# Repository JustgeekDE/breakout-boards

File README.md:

# breakout-boards
A variety of breakoutboards for various packages and modules

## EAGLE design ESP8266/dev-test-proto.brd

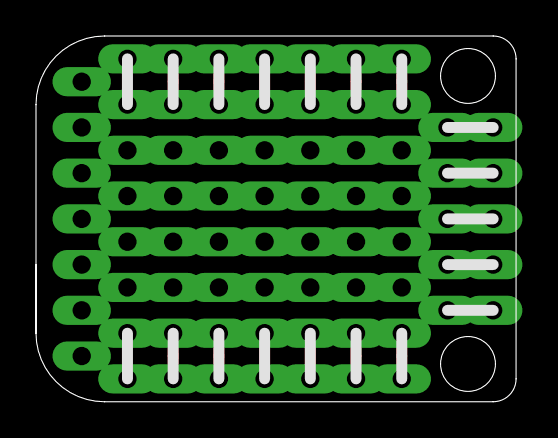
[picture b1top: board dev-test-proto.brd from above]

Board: 2 copper layers, 26.7 x 20.3 mm, 20 parts (0 on the bottom side), 19 nets.

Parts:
CON1, CON4, CON5, CON6, CON7, CON8, CON9, CON14, CON15, CON16, CON17, CON18, CON19, CON21, CON22: PINHEADER-100MIL-1X4-NOSILK
E$1, E$2, E$3: PINHEADER-100MIL-1X3-NOSILK
E$4, E$5: PINHEADER-100MIL-1X2-NOSILK

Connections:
+3V3: CON6.1, CON6.2
+5V: CON4.3, CON4.4
GND: CON21.3, CON21.4
GPIO0: CON22.1, CON22.2
GPIO2: CON15.1, CON15.2
GPIO12: CON14.1, CON14.2
GPIO13: CON7.1, CON7.2
GPIO14: CON1.1, CON1.2
GPIO15: CON18.1, CON18.2
GPIO16: CON8.3, CON8.4
RESET: CON9.3, CON9.4
RX: CON17.3, CON17.4
S$1: CON5.3, CON5.4
S$2: E$2.3, E$3.3
S$3: E$2.2, E$3.2
S$4: E$2.1, E$3.1
S$5: E$4.2, E$5.2
S$6: E$4.1, E$5.1
TX: CON16.3, CON16.4

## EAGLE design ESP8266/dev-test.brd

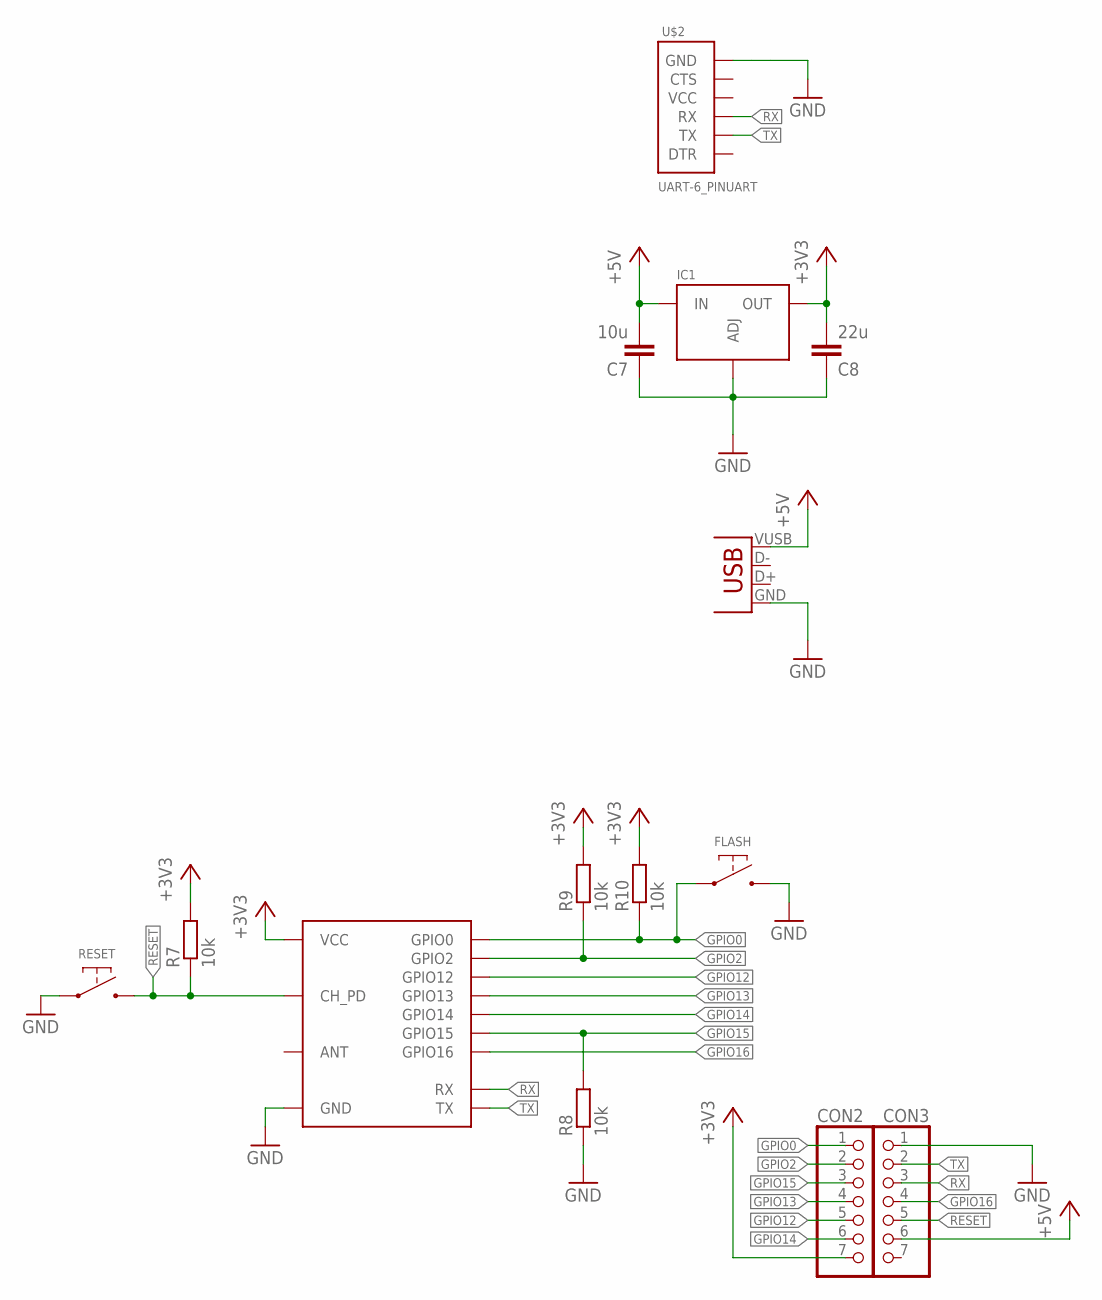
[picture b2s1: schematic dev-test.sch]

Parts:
C7: 10u; C0805
C8: 22u; C0805
CON1: USBMICRO-NO_CENTER; USB-MICRO-SMD-NO_CENTER
CON2, CON3: GENERIC-1X7THT; PINHEADER-100MIL-1X7
FLASH: SWITCH-DEFAULT_OFF-SMD-2_PIN; SWITCH-SMD-2_PIN-DX
IC1: REGULATOR-LM317-SOT223; SOT223
R7, R8, R9, R10: 10k; R0603
RESET: SWITCH-DEFAULT_OFF-SMD-2_PIN; SWITCH-SMD-2_PIN-DX
U$1: ESP8266-03; ESP8266-ESP-03
U$2: UART-6_PINUART; ANGLE-1X6

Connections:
+3V3: C8.2, CON2.7, IC1.2 (OUT), IC1.4 (OUT), R7.2, R9.2, R10.2, U$1.P$8 (VCC)
+5V: C7.2, CON1.VUSB (VBUS), CON3.6, IC1.3 (IN)
GND: C7.1, C8.1, CON1.GND, CON3.1, FLASH.P$2, IC1.1 (ADJ), R8.1, RESET.P$1, U$1.P$1 (GND), U$2.1 (GND)
GPIO0: CON2.1, FLASH.P$1, R10.1, U$1.P$14 (GPIO0)
GPIO2: CON2.2, R9.1, U$1.P$13 (GPIO2)
GPIO12: CON2.5, U$1.P$10 (GPIO12)
GPIO13: CON2.4, U$1.P$11 (GPIO13)
GPIO14: CON2.6, U$1.P$9 (GPIO14)
GPIO15: CON2.3, R8.2, U$1.P$12 (GPIO15)
GPIO16: CON3.4, U$1.P$5 (GPIO16)
RESET: CON3.5, R7.1, RESET.P$2, U$1.P$6 (CH_PD)
RX: CON3.3, U$1.P$4 (RX), U$2.4 (RX)
TX: CON3.2, U$1.P$3 (TX), U$2.5 (TX)

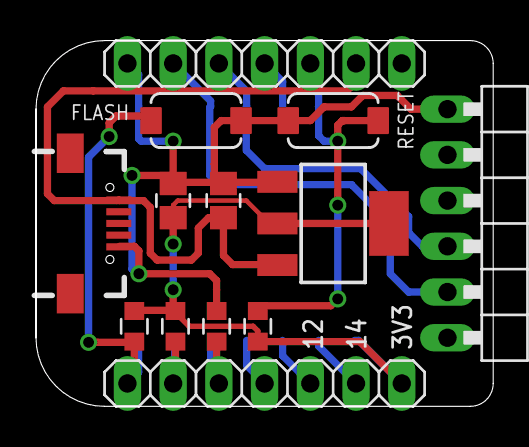
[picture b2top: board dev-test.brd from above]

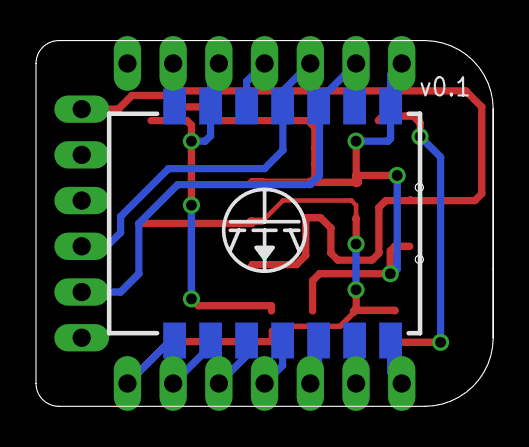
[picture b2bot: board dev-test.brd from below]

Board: 2 copper layers, 25.4 x 20.3 mm, 15 parts (2 on the bottom side), 13 nets.

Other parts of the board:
U$3: LOGO-JUSTGEEK-XS

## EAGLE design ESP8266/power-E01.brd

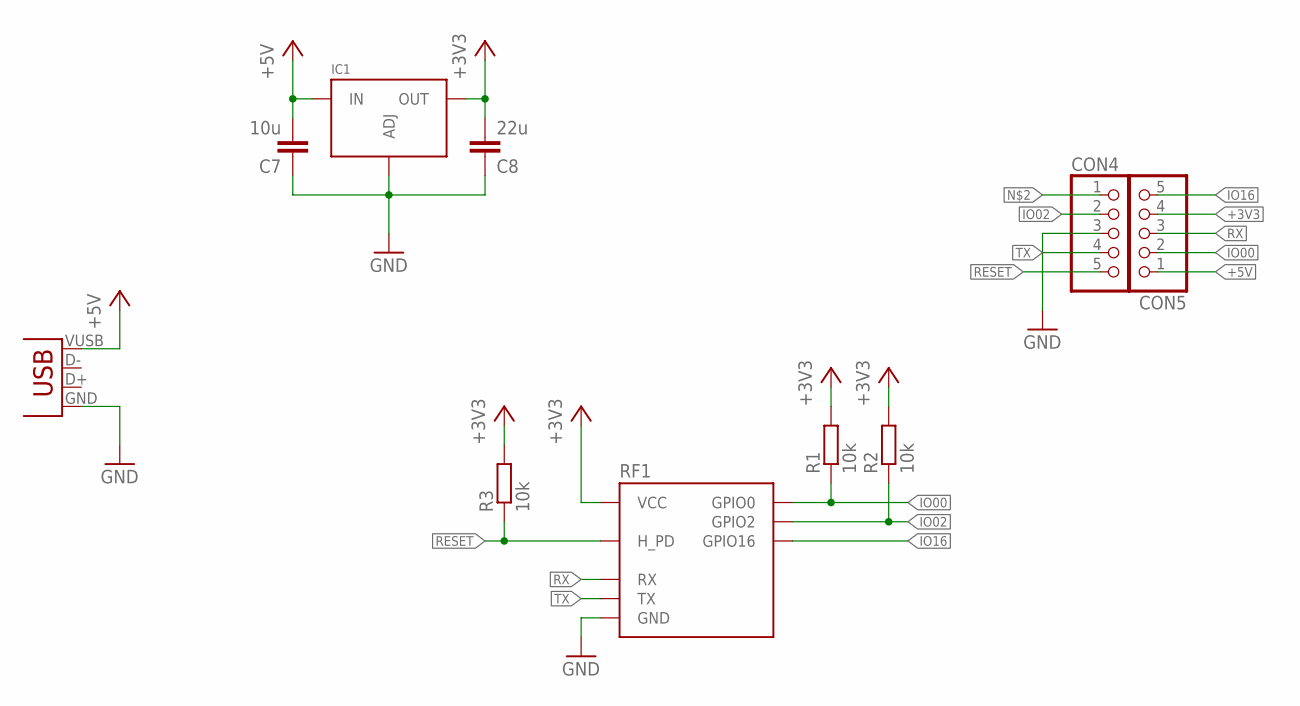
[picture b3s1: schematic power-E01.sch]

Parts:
C7: 10u; C0805
C8: 22u; C0805
CON1: USBMICRO-NO_CENTER; USB-MICRO-SMD-NO_CENTER
CON4, CON5: GENERIC-1X5; PINHEADER-100MIL-1X5-NOSILK
IC1: REGULATOR-LM317-SOT223; SOT223
R1, R2, R3: 10k; R0603
RF1: ESP2866-ESP-01THT-NOSILK; ESP8266-ESP-01-NOSILK

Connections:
+3V3: C8.2, CON5.4, IC1.2 (OUT), IC1.4 (OUT), R1.2, R2.2, R3.2, RF1.VCC
+5V: C7.2, CON1.VUSB (VBUS), CON5.1, IC1.3 (IN)
GND: C7.1, C8.1, CON1.GND, CON4.3, IC1.1 (ADJ), RF1.GND
IO00: CON5.2, R1.1, RF1.GPIO0
IO02: CON4.2, R2.1, RF1.GPIO2
IO16: CON5.5, RF1.GPIO16
RESET: CON4.5, R3.1, RF1.H_PD
RX: CON5.3, RF1.RX
TX: CON4.4, RF1.TX

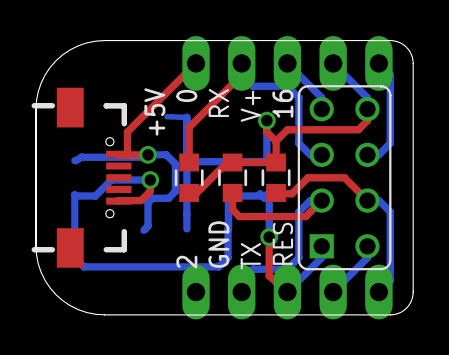
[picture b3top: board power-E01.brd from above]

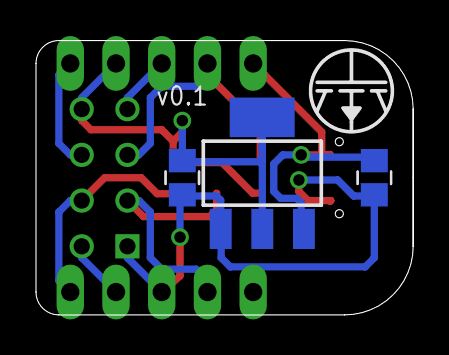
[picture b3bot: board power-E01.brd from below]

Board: 2 copper layers, 21.0 x 15.2 mm, 11 parts (4 on the bottom side), 9 nets.

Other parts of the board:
U$3: LOGO-JUSTGEEK-XS

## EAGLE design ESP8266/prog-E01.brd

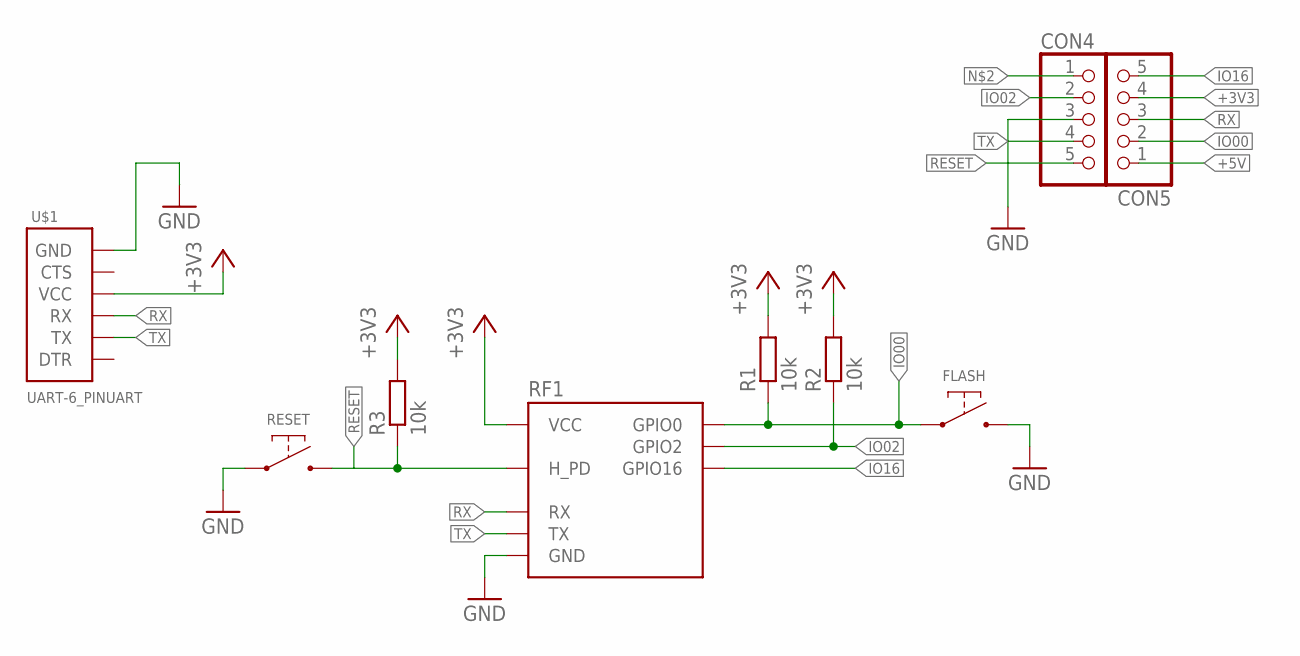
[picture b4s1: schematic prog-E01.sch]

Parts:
CON4, CON5: GENERIC-1X5; PINHEADER-100MIL-1X5-NOSILK
FLASH: SWITCH-DEFAULT_OFF-SMD-2_PIN; SWITCH-SMD-2_PIN-DX
R1, R2, R3: 10k; R0603
RESET: SWITCH-DEFAULT_OFF-SMD-2_PIN; SWITCH-SMD-2_PIN-DX
RF1: ESP2866-ESP-01THT-NOSILK; ESP8266-ESP-01-NOSILK
U$1: UART-6_PINUART; ANGLE-1X6

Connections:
+3V3: CON5.4, R1.2, R2.2, R3.2, RF1.VCC, U$1.3 (VCC)
+5V: CON5.1
GND: CON4.3, FLASH.P$2, RESET.P$1, RF1.GND, U$1.1 (GND)
IO00: CON5.2, FLASH.P$1, R1.1, RF1.GPIO0
IO02: CON4.2, R2.1, RF1.GPIO2
IO16: CON5.5, RF1.GPIO16
RESET: CON4.5, R3.1, RESET.P$2, RF1.H_PD
RX: CON5.3, RF1.RX, U$1.4 (RX)
TX: CON4.4, RF1.TX, U$1.5 (TX)

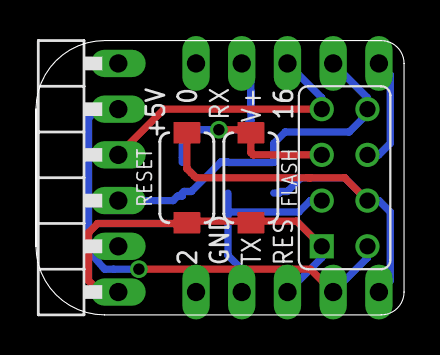
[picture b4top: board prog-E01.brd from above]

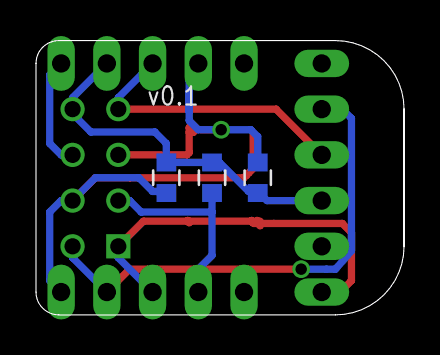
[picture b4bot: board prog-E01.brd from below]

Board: 2 copper layers, 20.4 x 15.2 mm, 9 parts (3 on the bottom side), 8 nets.

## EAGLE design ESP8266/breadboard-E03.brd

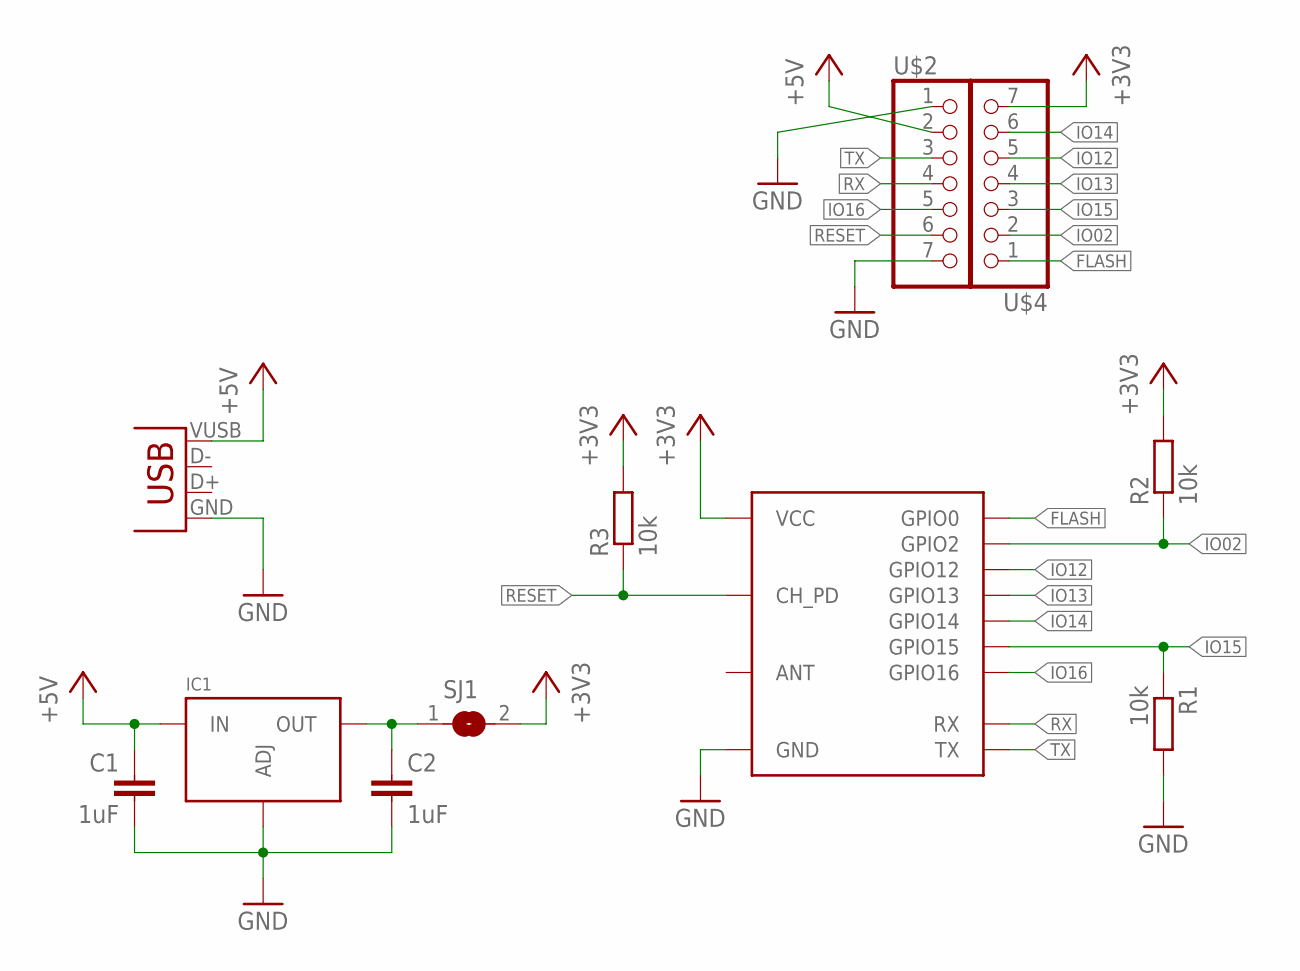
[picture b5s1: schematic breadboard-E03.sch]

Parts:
C1, C2: 1uF; C0805
CON1: USBMICRO-NO_CENTER; USB-MICRO-SMD-NO_CENTER
IC1: REGULATOR-TLV1117SOT223; SOT223
R1, R2, R3: 10k; R0603
SJ1: SJ
U$1: ESP8266-03; ESP8266-ESP-03
U$2, U$4: GENERIC-1X7; PINHEADER-100MIL-1X7

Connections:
+3V3: R2.2, R3.2, SJ1.2, U$1.P$8 (VCC), U$4.7
+5V: C1.1, CON1.VUSB (VBUS), IC1.3 (IN), U$2.2
FLASH: U$1.P$14 (GPIO0), U$4.1
GND: C1.2, C2.2, CON1.GND, IC1.1 (ADJ), R1.2, U$1.P$1 (GND), U$2.1, U$2.7
IO02: R2.1, U$1.P$13 (GPIO2), U$4.2
IO12: U$1.P$10 (GPIO12), U$4.5
IO13: U$1.P$11 (GPIO13), U$4.4
IO14: U$1.P$9 (GPIO14), U$4.6
IO15: R1.1, U$1.P$12 (GPIO15), U$4.3
IO16: U$1.P$5 (GPIO16), U$2.5
unnamed: C2.1, IC1.2 (OUT), IC1.4 (OUT), SJ1.1
RESET: R3.1, U$1.P$6 (CH_PD), U$2.6
RX: U$1.P$4 (RX), U$2.4
TX: U$1.P$3 (TX), U$2.3

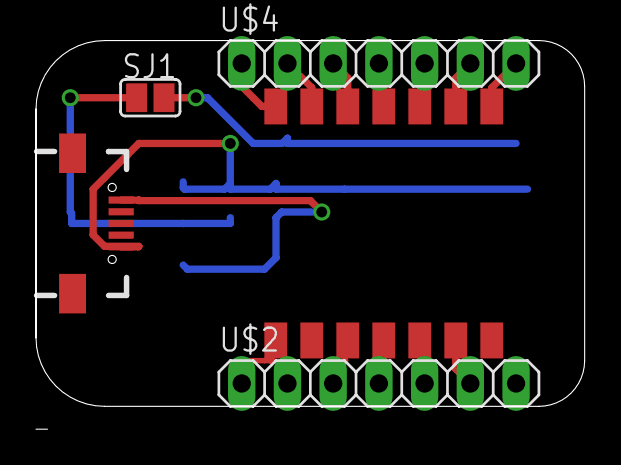
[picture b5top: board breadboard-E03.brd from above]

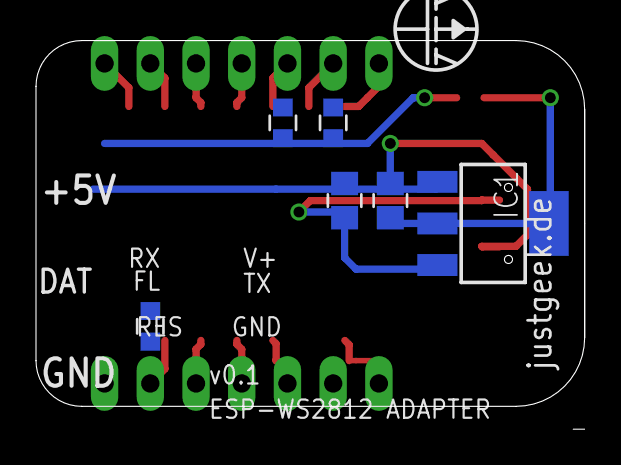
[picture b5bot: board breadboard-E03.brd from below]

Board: 2 copper layers, 30.5 x 21.6 mm, 12 parts (7 on the bottom side), 14 nets.

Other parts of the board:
U$3: LOGO-JUSTGEEK-XS

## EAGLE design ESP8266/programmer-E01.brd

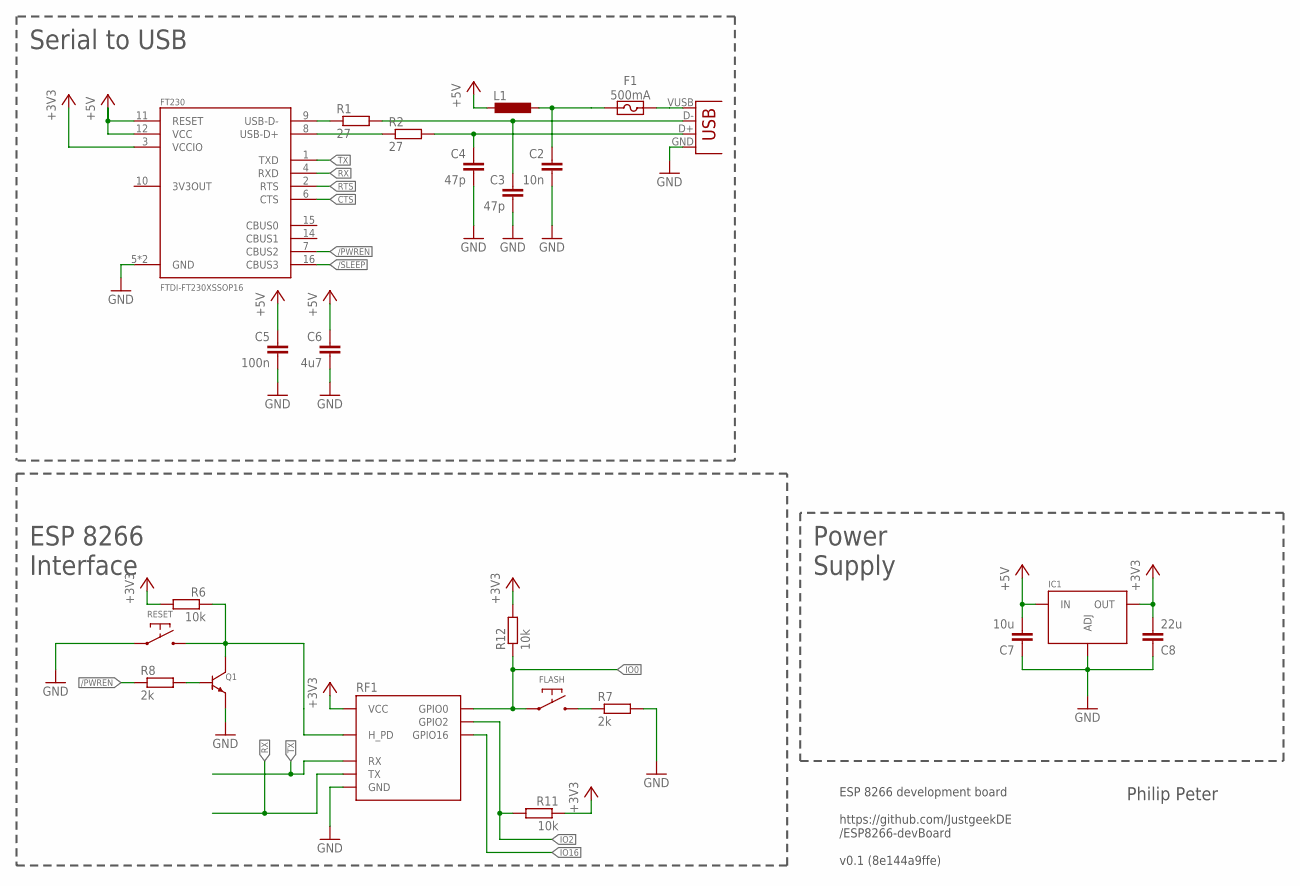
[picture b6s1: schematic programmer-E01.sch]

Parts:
C2: 10n; C0805
C3, C4: 47p; C0805
C5: 100n; C0805
C6: 4u7; C0805
C7: 10u; C0805
C8: 22u; C0805
CON1: USBMICRO-NO_CENTER-LONG_PADS; USB-MICRO-SMD-NO_CENTER-LONG_PADS
F1: 500mA; SMD-FUSE-0805
FLASH: SWITCH-DEFAULT_OFF-2PIN; SWITCH-GENERIC-2_PIN
FT230: FTDI-FT230XSSOP16; SSOP-16-FTDI
IC1: REGULATOR-LM317-SOT223; SOT223
L1: 875-MI0805K601R-10; R0805
Q1: TRANSISTOR-NPN-GENERIC-SOT23-BEC; SOT23
R1, R2: 27; R0805
R6, R11, R12: 10k; R0805
R7, R8: 2k; R0805
RESET: SWITCH-DEFAULT_OFF-2PIN; SWITCH-GENERIC-2_PIN
RF1: ESP2866-ESP-01THT; ESP8266-ESP-01

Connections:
+3V3: C8.2, FT230.3 (VCCIO), IC1.2 (OUT), IC1.4 (OUT), R6.2, R11.1, R12.2, RF1.VCC
+5V: C5.1, C6.1, C7.2, FT230.11 (RESET), FT230.12 (VCC), IC1.3 (IN), L1.2
/PWREN: FT230.7 (CBUS2), R8.1
/SLEEP: FT230.16 (CBUS3)
CTS: FT230.6 (CTS)
GND: C2.2, C3.2, C4.2, C5.2, C6.2, C7.1, C8.1, CON1.GND, FT230.5 (GND), FT230.13 (GND), IC1.1 (ADJ), Q1.P$2 (EMITTER), R7.2, RESET.P$1, RF1.GND
IO0: FLASH.P$1, R12.1, RF1.GPIO0
IO2: R11.2, RF1.GPIO2
IO16: RF1.GPIO16
unnamed: Q1.P$1 (BASE), R8.2
unnamed: C2.1, F1.1, L1.1
unnamed: C3.1, CON1.D-, R1.2
unnamed: FT230.9 (USB-D-), R1.1
unnamed: FT230.8 (USB-D+), R2.1
unnamed: C4.1, CON1.D+, R2.2
unnamed: FLASH.P$2, R7.1
unnamed: CON1.VUSB (VBUS), F1.2
RESET: Q1.P$3 (COLLECTOR), R6.1, RESET.P$2, RF1.H_PD
RTS: FT230.2 (RTS)
RX: FT230.4 (RXD), RF1.TX
TX: FT230.1 (TXD), RF1.RX

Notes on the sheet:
ESP 8266 Interface
Power Supply
Philip Peter
ESP 8266 development board https://github.com/JustgeekDE /ESP8266-devBoard v0.1 (8e144a9ffe)
Serial to USB

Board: 2 copper layers, 23 parts (0 on the bottom side), 17 nets, no tracks yet.

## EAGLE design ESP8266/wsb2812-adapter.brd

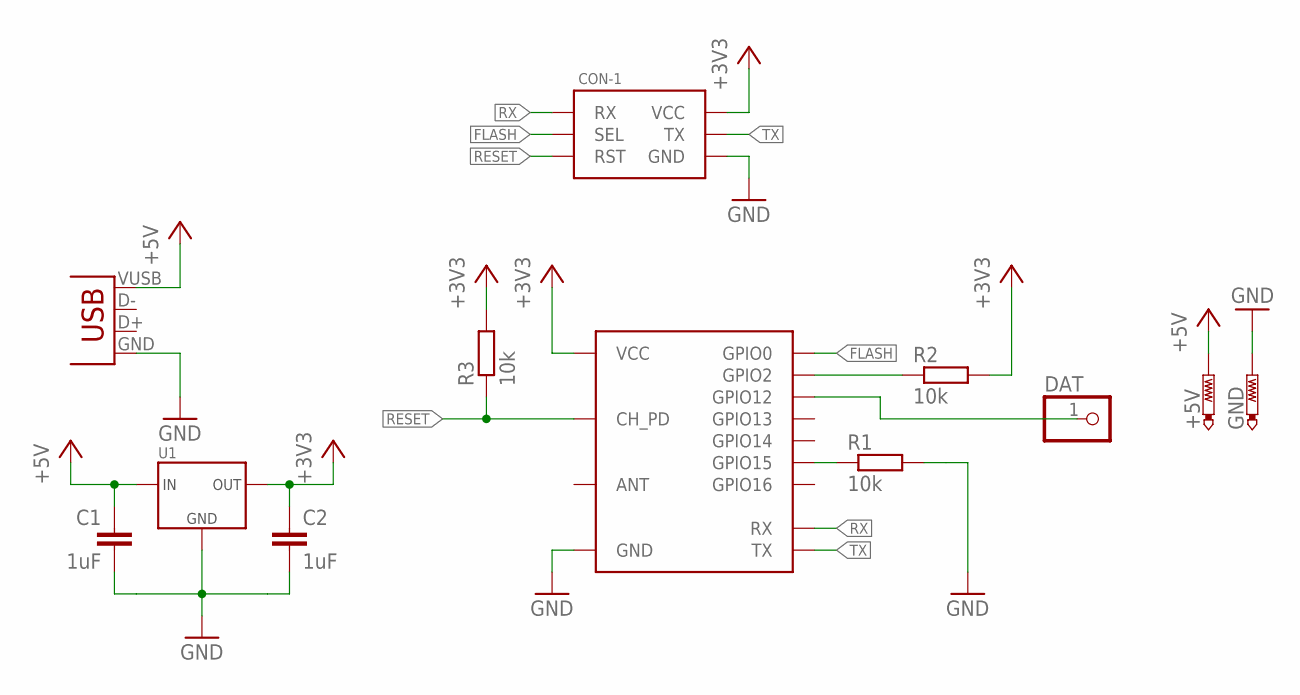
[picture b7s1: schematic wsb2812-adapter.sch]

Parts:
+5V: PTR1PAD1-20; P1-20
C1, C2: 1uF; C0805
CON1: USBMICRO-NO_CENTER; USB-MICRO-SMD-NO_CENTER
CON-1: ESP8266-6_PIN-POGO; POGO-1.27-6_PIN-MADWORM
DAT: PINHD-1X1; 1X01
GND: PTR1PAD1-20; P1-20
R1, R2, R3: 10k; R0603
U1: REGULATOR-XC6206SOT23; SOT23
U$1: ESP8266-03; ESP8266-ESP-03

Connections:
+3V3: C2.1, CON-1.P$2 (VCC), R2.2, R3.2, U1.P$2 (OUT), U$1.P$8 (VCC)
+5V: +5V.TP, C1.1, CON1.VUSB (VBUS), U1.P$3 (IN)
FLASH: CON-1.P$3 (SEL), U$1.P$14 (GPIO0)
GND: C1.2, C2.2, CON1.GND, CON-1.P$6 (GND), GND.TP, R1.2, U1.P$1 (GND), U$1.P$1 (GND)
unnamed: R1.1, U$1.P$12 (GPIO15)
unnamed: DAT.1, U$1.P$10 (GPIO12)
unnamed: R2.1, U$1.P$13 (GPIO2)
RESET: CON-1.P$5 (RST), R3.1, U$1.P$6 (CH_PD)
RX: CON-1.P$1 (RX), U$1.P$4 (RX)
TX: CON-1.P$4 (TX), U$1.P$3 (TX)

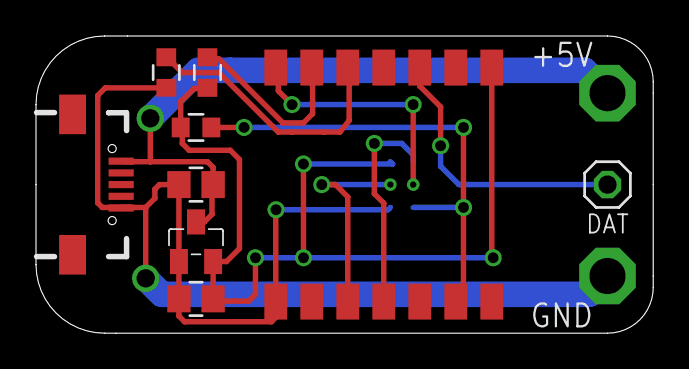
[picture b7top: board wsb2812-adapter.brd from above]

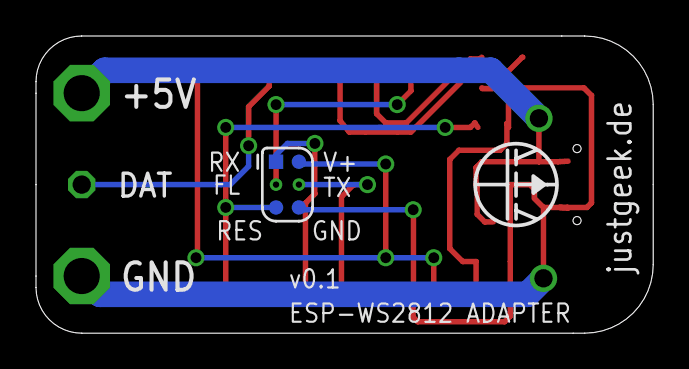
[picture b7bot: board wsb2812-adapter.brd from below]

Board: 2 copper layers, 34.3 x 16.5 mm, 13 parts (2 on the bottom side), 10 nets.

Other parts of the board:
U$3: LOGO-JUSTGEEK-XS

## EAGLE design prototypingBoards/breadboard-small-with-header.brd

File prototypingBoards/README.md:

# Breadboard breakouts
Some generic prototyping boards, mimicking the common breadboard design, with additional space for USB and barrel jack sockets.

The small boards fit the [SoB 5x5](http://dangerousprototypes.com/docs/Sick_of_Beige_standard_PCB_sizes_v1.0) footprint, while the large ones are twice as long.

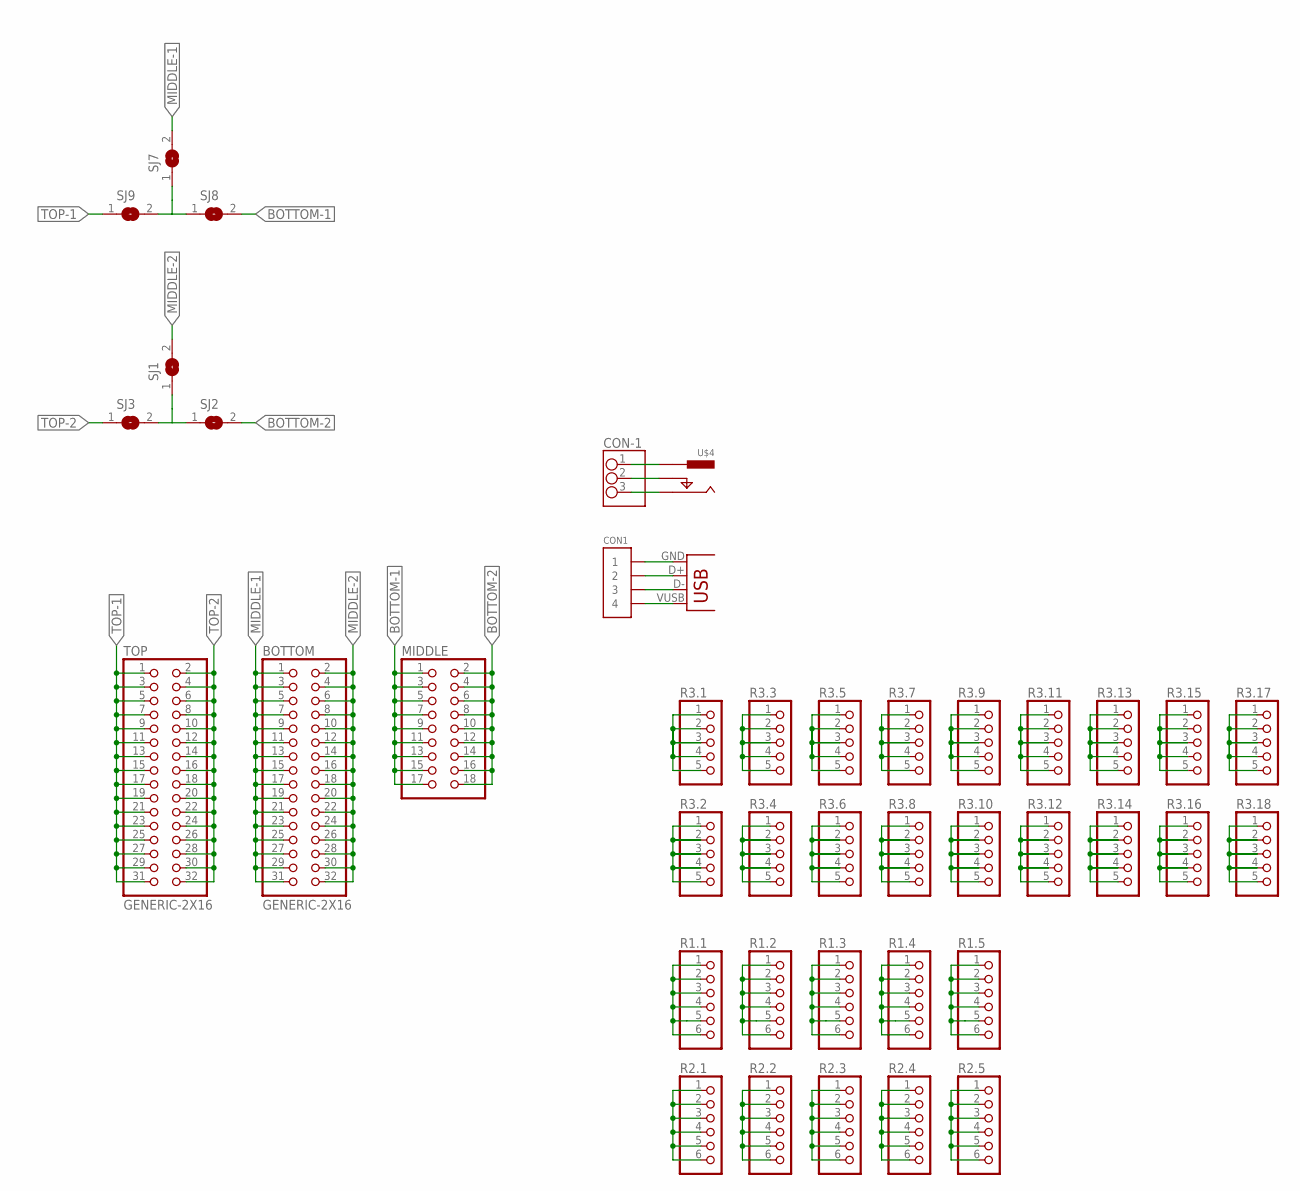
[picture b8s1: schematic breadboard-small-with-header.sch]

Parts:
BOTTOM: GENERIC-2X16; PINHEADER-100MIL-2X16-NOSILK
CON1: GENERIC-1X4STRAIGHT; PINHEADER-100MIL-1X4-NOSILK
CON-1: GENERIC-1X3; PINHEADER-100MIL-1X3-NOSILK
MIDDLE: GENERIC-2X9; PINHEADER-100MIL-2X9-NOSILK
R1.1, R1.2, R1.3, R1.4, R1.5, R2.1, R2.2, R2.3, R2.4, R2.5: GENERIC-1X6; PINHEADER-100MIL-1X6-NOSILK
R3.1, R3.2, R3.3, R3.4, R3.5, R3.6, R3.7, R3.8, R3.9, R3.10, R3.11, R3.12, R3.13, R3.14, R3.15, R3.16, R3.17, R3.18: GENERIC-1X5; PINHEADER-100MIL-1X5-NOSILK
SJ1, SJ2, SJ3, SJ7, SJ8, SJ9: SJ
TOP: GENERIC-2X16; PINHEADER-100MIL-2X16-NOSILK
U$3: USBMINI; CONN_USB_MINI-B
U$4: POWER-BARREL_JACKEBAY; POWER-BARREL-2MM1-EBAY

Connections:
BOTTOM-1: MIDDLE.1, MIDDLE.3, MIDDLE.5, MIDDLE.7, MIDDLE.9, MIDDLE.11, MIDDLE.13, MIDDLE.15, MIDDLE.17, SJ8.2
BOTTOM-2: MIDDLE.2, MIDDLE.4, MIDDLE.6, MIDDLE.8, MIDDLE.10, MIDDLE.12, MIDDLE.14, MIDDLE.16, MIDDLE.18, SJ2.2
CENTER: CON-1.1, U$4.P$4 (CENTER)
MIDDLE-1: BOTTOM.1, BOTTOM.3, BOTTOM.5, BOTTOM.7, BOTTOM.9, BOTTOM.11, BOTTOM.13, BOTTOM.15, BOTTOM.17, BOTTOM.19, BOTTOM.21, BOTTOM.23, BOTTOM.25, BOTTOM.27, BOTTOM.29, BOTTOM.31, SJ7.2
MIDDLE-2: BOTTOM.2, BOTTOM.4, BOTTOM.6, BOTTOM.8, BOTTOM.10, BOTTOM.12, BOTTOM.14, BOTTOM.16, BOTTOM.18, BOTTOM.20, BOTTOM.22, BOTTOM.24, BOTTOM.26, BOTTOM.28, BOTTOM.30, BOTTOM.32, SJ1.2
unnamed: R3.1.1, R3.1.2, R3.1.3, R3.1.4, R3.1.5
unnamed: R3.2.1, R3.2.2, R3.2.3, R3.2.4, R3.2.5
unnamed: R2.1.1, R2.1.2, R2.1.3, R2.1.4, R2.1.5, R2.1.6
unnamed: R1.1.1, R1.1.2, R1.1.3, R1.1.4, R1.1.5, R1.1.6
unnamed: R2.3.1, R2.3.2, R2.3.3, R2.3.4, R2.3.5, R2.3.6
unnamed: R2.2.1, R2.2.2, R2.2.3, R2.2.4, R2.2.5, R2.2.6
unnamed: R1.2.1, R1.2.2, R1.2.3, R1.2.4, R1.2.5, R1.2.6
unnamed: R1.3.1, R1.3.2, R1.3.3, R1.3.4, R1.3.5, R1.3.6
unnamed: R2.4.1, R2.4.2, R2.4.3, R2.4.4, R2.4.5, R2.4.6
unnamed: R1.4.1, R1.4.2, R1.4.3, R1.4.4, R1.4.5, R1.4.6
unnamed: R2.5.1, R2.5.2, R2.5.3, R2.5.4, R2.5.5, R2.5.6
unnamed: R1.5.1, R1.5.2, R1.5.3, R1.5.4, R1.5.5, R1.5.6
unnamed: R3.3.1, R3.3.2, R3.3.3, R3.3.4, R3.3.5
unnamed: R3.4.1, R3.4.2, R3.4.3, R3.4.4, R3.4.5
unnamed: R3.5.1, R3.5.2, R3.5.3, R3.5.4, R3.5.5
unnamed: R3.6.1, R3.6.2, R3.6.3, R3.6.4, R3.6.5
unnamed: R3.7.1, R3.7.2, R3.7.3, R3.7.4, R3.7.5
unnamed: R3.8.1, R3.8.2, R3.8.3, R3.8.4, R3.8.5
unnamed: R3.9.1, R3.9.2, R3.9.3, R3.9.4, R3.9.5
unnamed: R3.10.1, R3.10.2, R3.10.3, R3.10.4, R3.10.5
unnamed: R3.11.1, R3.11.2, R3.11.3, R3.11.4, R3.11.5
unnamed: R3.12.1, R3.12.2, R3.12.3, R3.12.4, R3.12.5
unnamed: R3.13.1, R3.13.2, R3.13.3, R3.13.4, R3.13.5
unnamed: R3.14.1, R3.14.2, R3.14.3, R3.14.4, R3.14.5
unnamed: R3.15.1, R3.15.2, R3.15.3, R3.15.4, R3.15.5
unnamed: R3.16.1, R3.16.2, R3.16.3, R3.16.4, R3.16.5
unnamed: R3.17.1, R3.17.2, R3.17.3, R3.17.4, R3.17.5
unnamed: R3.18.1, R3.18.2, R3.18.3, R3.18.4, R3.18.5
unnamed: SJ1.1, SJ2.1, SJ3.2
unnamed: SJ7.1, SJ8.1, SJ9.2
SLEEVE: CON-1.3, U$4.P$3 (OUTER)
SWITCH: CON-1.2, U$4.P$2 (SWITCH)
TOP-1: SJ9.1, TOP.1, TOP.3, TOP.5, TOP.7, TOP.9, TOP.11, TOP.13, TOP.15, TOP.17, TOP.19, TOP.21, TOP.23, TOP.25, TOP.27, TOP.29, TOP.31
TOP-2: SJ3.1, TOP.2, TOP.4, TOP.6, TOP.8, TOP.10, TOP.12, TOP.14, TOP.16, TOP.18, TOP.20, TOP.22, TOP.24, TOP.26, TOP.28, TOP.30, TOP.32
USB-D+: CON1.2, U$3.D+
USB-DI: CON1.3, U$3.D-
USB-GND: CON1.1, U$3.GND
USB-V+: CON1.4, U$3.VUSB (VBUS)

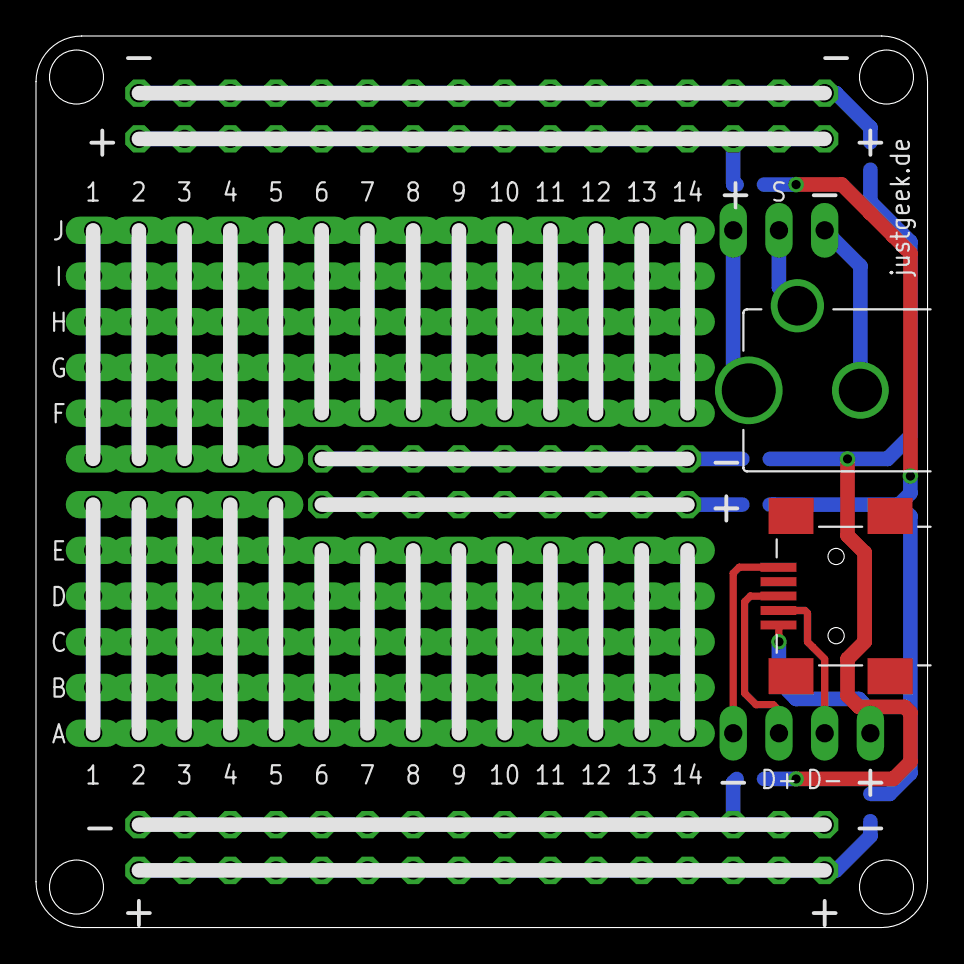
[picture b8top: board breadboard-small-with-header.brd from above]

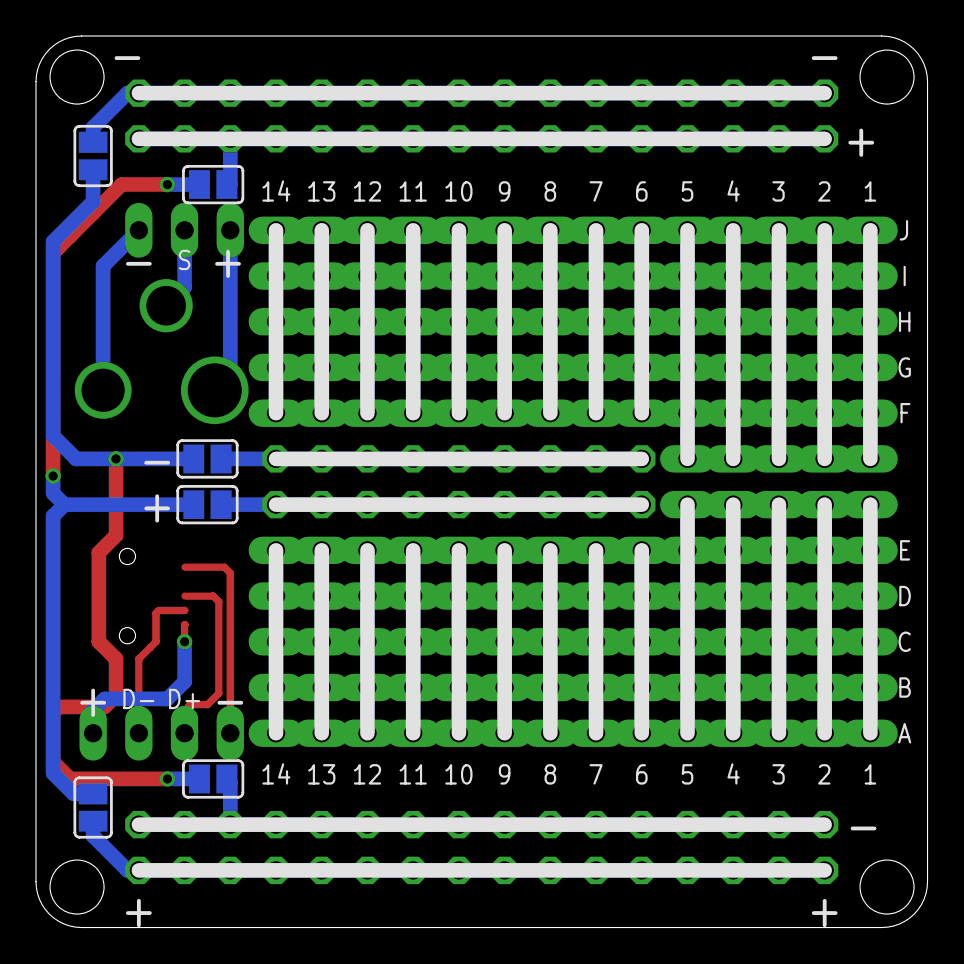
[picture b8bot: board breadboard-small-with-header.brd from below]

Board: 2 copper layers, 49.5 x 49.5 mm, 41 parts (6 on the bottom side), 43 nets.

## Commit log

2015-04-02 initial checkin
2015-04-05 Added gerber files to ignore list
2015-04-05 Cleaned up boards
2015-06-22 Some basic ESP8266 boards
2015-06-24 added power supply
2015-06-24 V0.1 done
2016-05-08 Some generic ESP 8266 breakout boards WIP
2016-08-14 switch to different vreg
2016-08-14 Added some adapters for ESP8266 01 module
2017-03-27 Add new ESP8266-03 breakout board
